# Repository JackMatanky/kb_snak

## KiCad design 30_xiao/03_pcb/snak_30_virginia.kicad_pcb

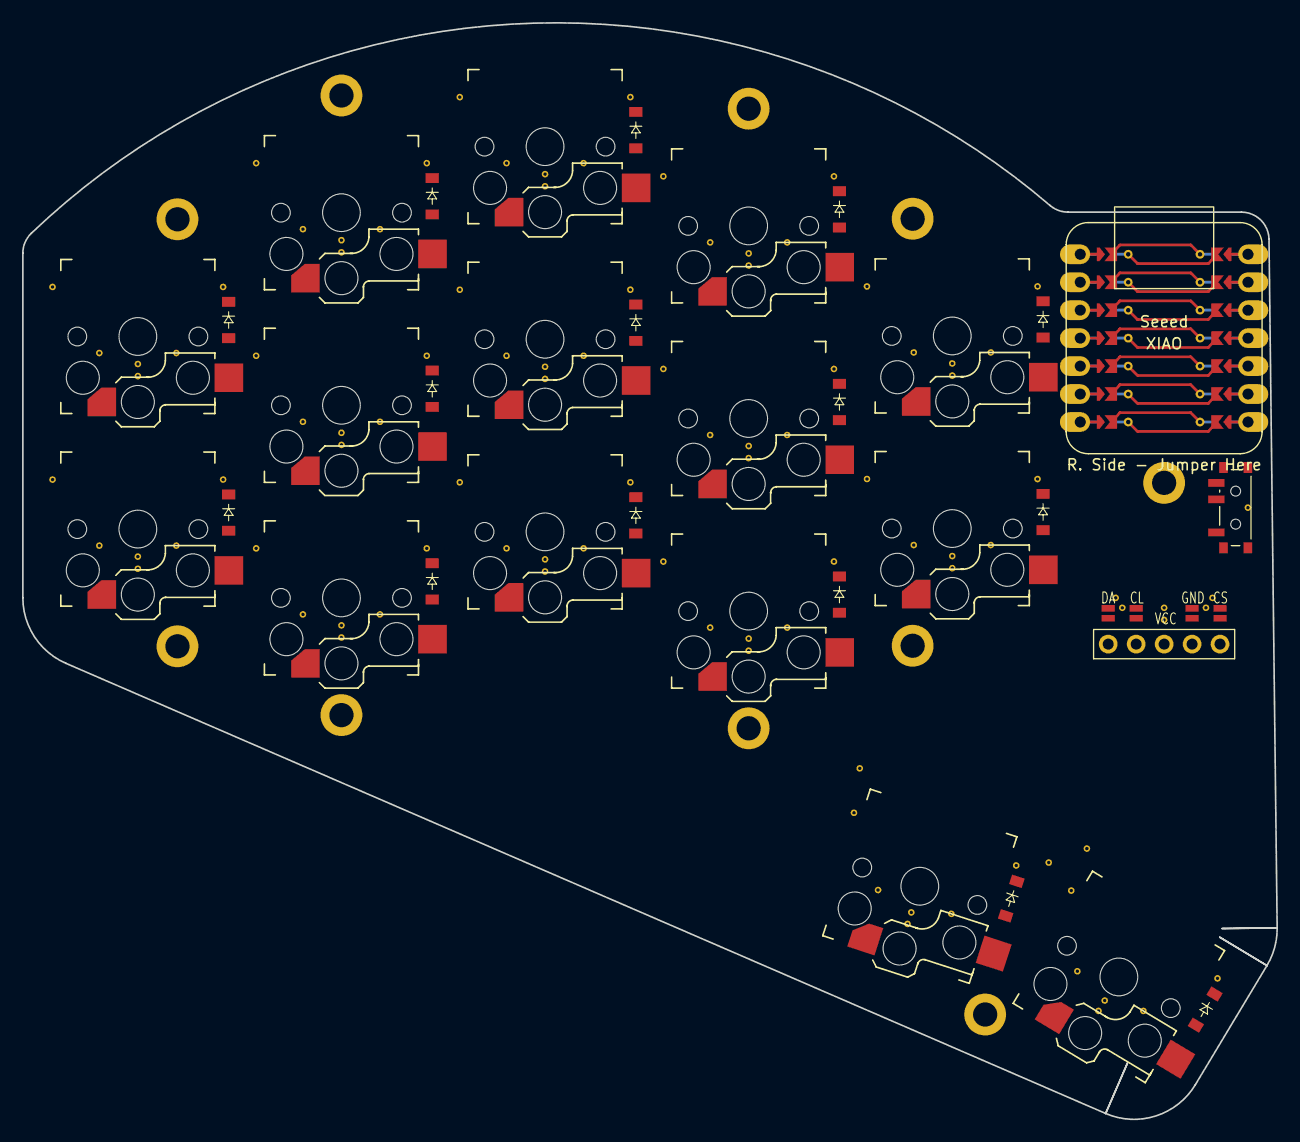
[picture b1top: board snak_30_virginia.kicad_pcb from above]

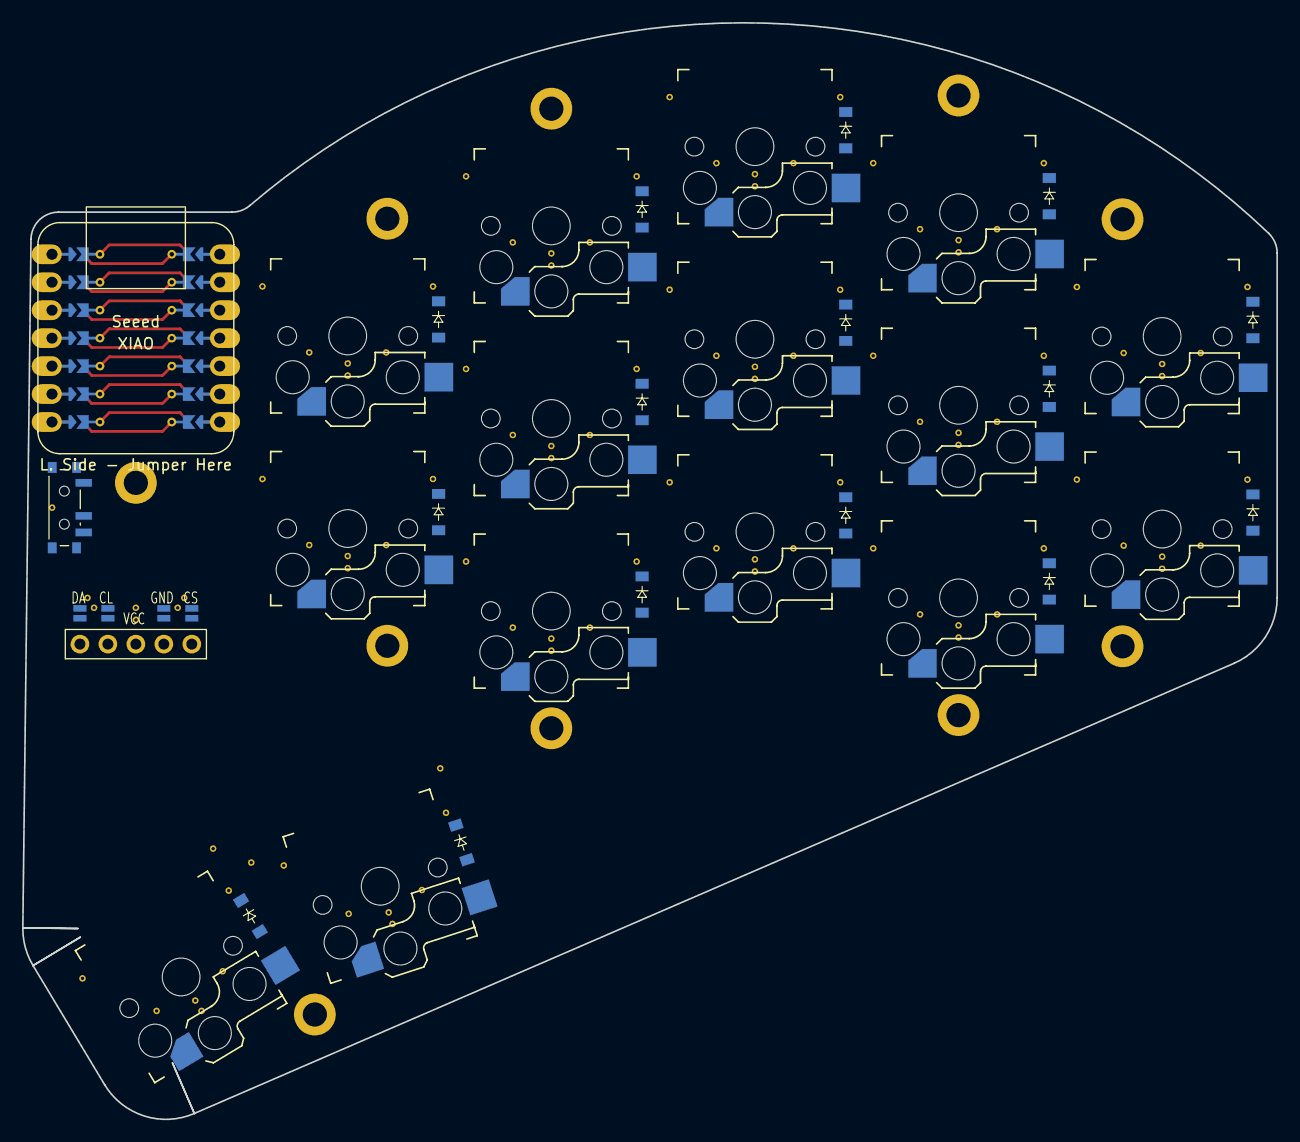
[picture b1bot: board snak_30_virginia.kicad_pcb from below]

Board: 2 copper layers, 114.0 x 99.6 mm, 57 parts (15 on the bottom side), 33 nets.

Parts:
D1, D2, D3, D4, D5, D6, D7, D8, D9, D10, D11, D12, D13, D14, D15, D16, D17, D18, D19, D20, D21, D22, D23, D24, D25, D26, D27, D28, D29, D30: diode_tht_sod123
DISP1: nice!view
H1, H2, H3, H4, H5, H6, H7, H8, H9, H10: mounting_hole
S1, S2, S3, S4, S5, S6, S7, S8, S9, S10, S11, S12, S13, S14, S15: PG1350
SW1: power_switch

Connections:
BAT_POS: SW1.2, SW1.5
C1: S1.1, S2.1, S3.1
C2: S4.1, S5.1, S6.1
C3: S7.1, S8.1, S9.1
C4: S10.1, S11.1, S14.1
C5: S12.1, S13.1, S15.1
DISP1_1: DISP1.1, DISP1.10, DISP1.23
DISP1_2: DISP1.2, DISP1.11, DISP1.22
DISP1_4: DISP1.4, DISP1.12, DISP1.21
DISP1_5: DISP1.5, DISP1.13, DISP1.20
DPC: DISP1.15, DISP1.25
DPD: DISP1.14, DISP1.24
DPE: DISP1.17, DISP1.27
GND: DISP1.16, DISP1.26
R1: D2.1, D5.1, D8.1, D11.1, D13.1, D17.1, D20.1, D23.1, D26.1, D28.1
R2: D1.1, D4.1, D7.1, D10.1, D12.1, D16.1, D19.1, D22.1, D25.1, D27.1
R3: D3.1, D6.1, D9.1, D14.1, D15.1, D18.1, D21.1, D24.1, D29.1, D30.1
RAW3V3: SW1.3, SW1.6
in_home: D15.2, D30.2, S15.2
index_bot: D9.2, D24.2, S9.2
index_mid: D10.2, D25.2, S10.2
index_top: D11.2, D26.2, S11.2
inner_mid: D12.2, D27.2, S12.2
inner_top: D13.2, D28.2, S13.2
middle_bot: D6.2, D21.2, S6.2
middle_mid: D7.2, D22.2, S7.2
middle_top: D8.2, D23.2, S8.2
out_home: D14.2, D29.2, S14.2
pinky_mid: D1.2, D16.2, S1.2
pinky_top: D2.2, D17.2, S2.2
ring_bot: D3.2, D18.2, S3.2
ring_mid: D4.2, D19.2, S4.2
ring_top: D5.2, D20.2, S5.2

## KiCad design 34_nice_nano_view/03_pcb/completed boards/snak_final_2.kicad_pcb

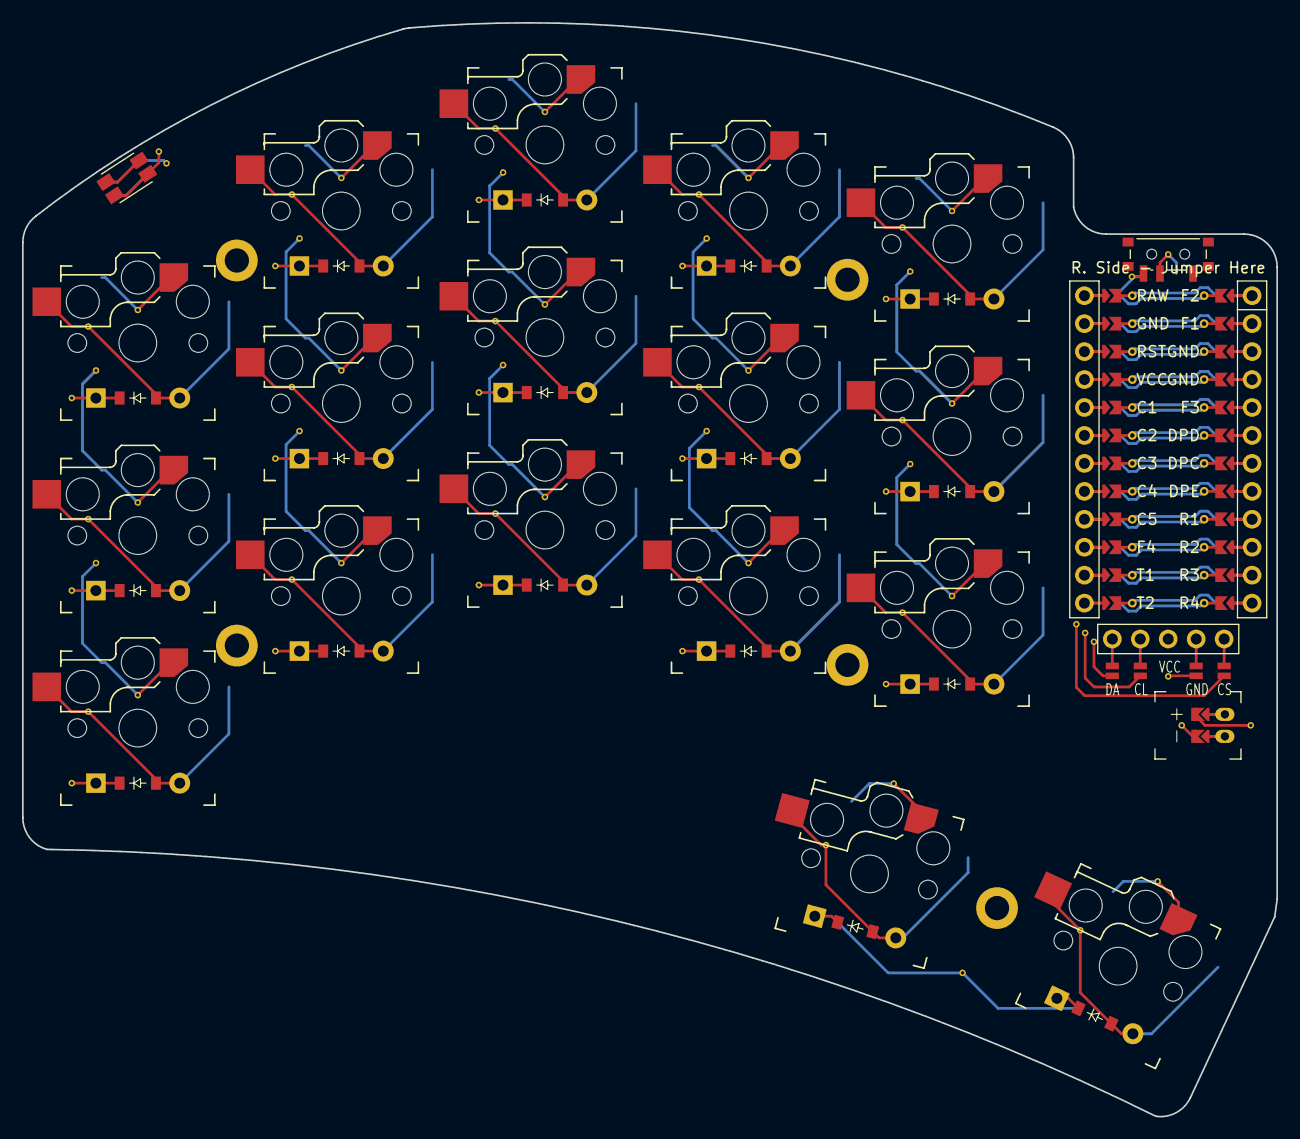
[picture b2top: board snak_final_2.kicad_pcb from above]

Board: 2 copper layers, 114.0 x 99.4 mm, 44 parts (0 on the bottom side), 42 nets.

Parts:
D1, D2, D3, D4, D5, D6, D7, D8, D9, D10, D11, D12, D13, D14, D15, D16, D17: ComboDiode
DISP1: nice!view
H1, H2, H3, H4, H5: mounting_hole
JST1: JST_PH_S2B-PH-K
MCU1: nice_nano
S1, S2, S3, S4, S5, S6, S7, S8, S9, S10, S11, S12, S13, S14, S15, S16, S17: PG1350
SW1: power_switch
SW2: sw_reset_side

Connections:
C1: MCU1.5, S1.1, S2.1, S3.1
C2: MCU1.6, S4.1, S5.1, S6.1
C3: MCU1.7, S7.1, S8.1, S9.1
C4: MCU1.8, S10.1, S11.1, S12.1
C5: MCU1.9, S13.1, S14.1, S15.1
DISP1_1: DISP1.1, DISP1.14, DISP1.27
DISP1_2: DISP1.2, DISP1.15, DISP1.26
DISP1_4: DISP1.4, DISP1.16, DISP1.25
DISP1_5: DISP1.5, DISP1.17, DISP1.24
DPC: DISP1.11, DISP1.21, MCU1.118
DPD: DISP1.10, DISP1.20, MCU1.119
DPE: DISP1.13, DISP1.23, MCU1.117
GND: DISP1.12, DISP1.22, JST1.1, MCU1.2, MCU1.121, MCU1.122, SW2.1
JST1_1: JST1.11, JST1.21, JST1.31
JST1_2: JST1.12, JST1.22, JST1.32
R1: D3.1, D6.1, D9.1, D12.1, D15.1, MCU1.116
R2: D2.1, D5.1, D8.1, D11.1, D14.1, MCU1.115
R3: D1.1, D4.1, D7.1, D10.1, D13.1, MCU1.114
R4: D16.1, D17.1, MCU1.113
RAW: MCU1.1, SW1.3, SW1.6
RST: MCU1.3, SW2.2
T1: MCU1.11, S16.1
T2: MCU1.12, S17.1
VCC: DISP1.3, MCU1.4
in_home: D17.2, S17.2
index_bot: D10.2, S10.2
index_mid: D11.2, S11.2
index_top: D12.2, S12.2
inner_bot: D13.2, S13.2
inner_mid: D14.2, S14.2
inner_top: D15.2, S15.2
middle_bot: D7.2, S7.2
middle_mid: D8.2, S8.2
middle_top: D9.2, S9.2
out_home: D16.2, S16.2
pinky_bot: D1.2, S1.2
pinky_mid: D2.2, S2.2
pinky_top: D3.2, S3.2
pos: JST1.2, SW1.2, SW1.5
ring_bot: D4.2, S4.2
ring_mid: D5.2, S5.2
ring_top: D6.2, S6.2

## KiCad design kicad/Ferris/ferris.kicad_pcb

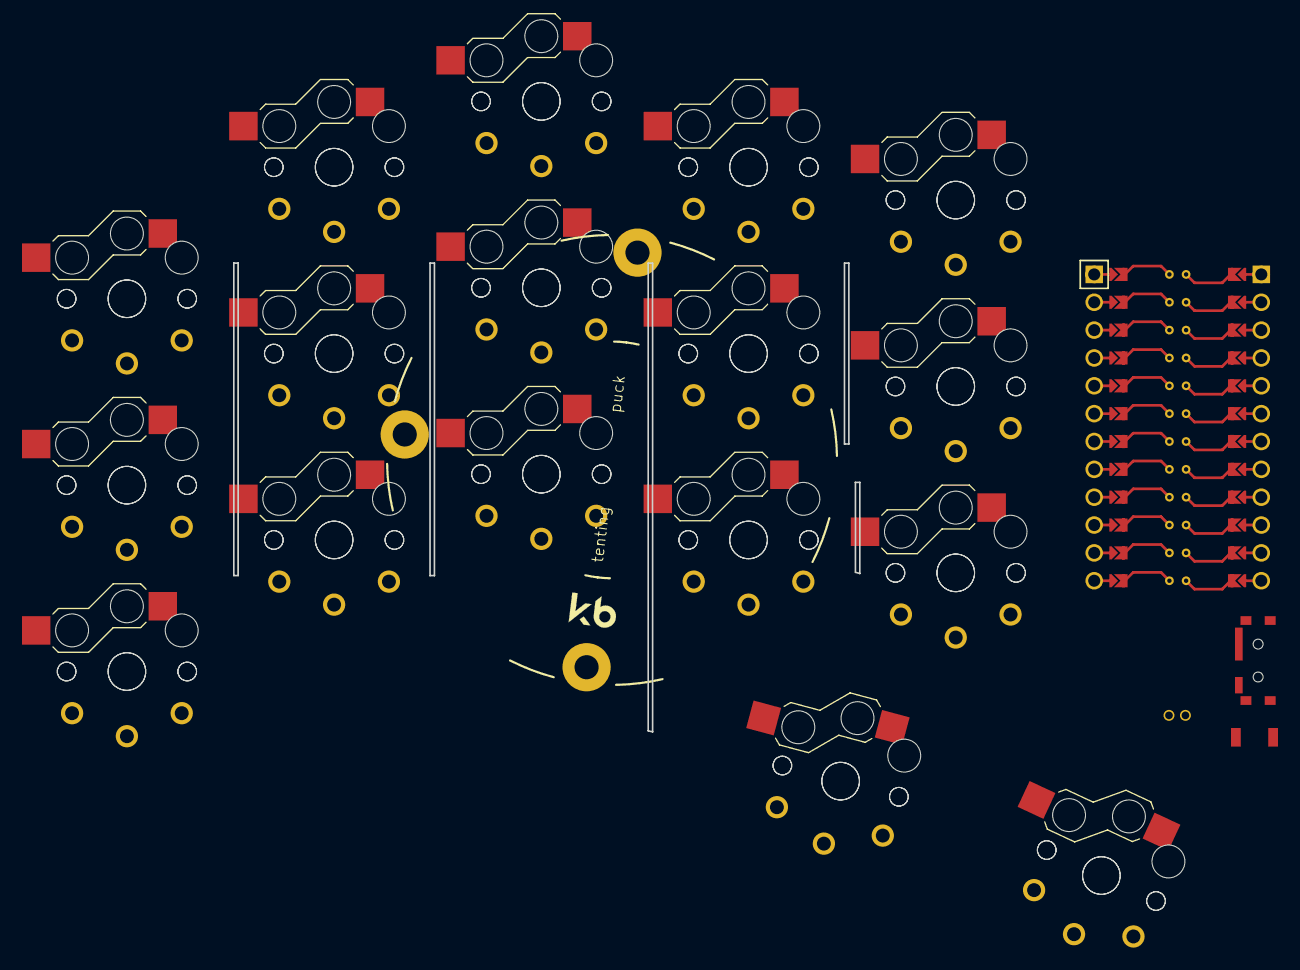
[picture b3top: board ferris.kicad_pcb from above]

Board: 2 copper layers, 36 parts (0 on the bottom side), 18 nets, no tracks yet.

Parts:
MCU1: ProMicro
S1, S2, S3, S4, S5, S6, S7, S8, S9, S10, S11, S12, S13, S14, S15, S16, S17, S18, S19, S20, S21, S22, S23, S24, S25, S26, S27, S28, S29, S30, S31, S32, S33, S34: PG1350
_1: Tenting Puck

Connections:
GND: MCU1.2, MCU1.21, MCU1.22, S1.2, S2.2, S3.2, S4.2, S5.2, S6.2, S7.2, S8.2, S9.2, S10.2, S11.2, S12.2, S13.2, S14.2, S15.2, S16.2, S17.2, S18.2, S19.2, S20.2, S21.2, S22.2, S23.2, S24.2, S25.2, S26.2, S27.2, S28.2, S29.2, S30.2, S31.2, S32.2, S33.2, S34.2
P0: MCU1.23, S9.1, S26.1
P1: MCU1.24, S15.1, S32.1
P2: MCU1.20, S3.1, S20.1
P3: MCU1.19, S14.1, S31.1
P4: MCU1.18, S8.1, S25.1
P5: MCU1.17, S2.1, S19.1
P6: MCU1.16, S13.1, S30.1
P7: MCU1.15, S7.1, S24.1
P8: MCU1.14, S1.1, S18.1
P9: MCU1.13, S16.1, S33.1
P10: MCU1.12, S17.1, S34.1
P14: MCU1.10, S4.1, S21.1
P15: MCU1.9, S10.1, S27.1
P18: MCU1.8, S5.1, S22.1
P19: MCU1.7, S11.1, S28.1
P20: MCU1.6, S6.1, S23.1
P21: MCU1.5, S12.1, S29.1
